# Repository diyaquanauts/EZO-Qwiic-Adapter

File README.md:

# EZO Qwiic Adapter
This is a simple qwiic I2C adapter for Atlas Scientifics isolated carrier board.
## Assembled Board

## Bare Board

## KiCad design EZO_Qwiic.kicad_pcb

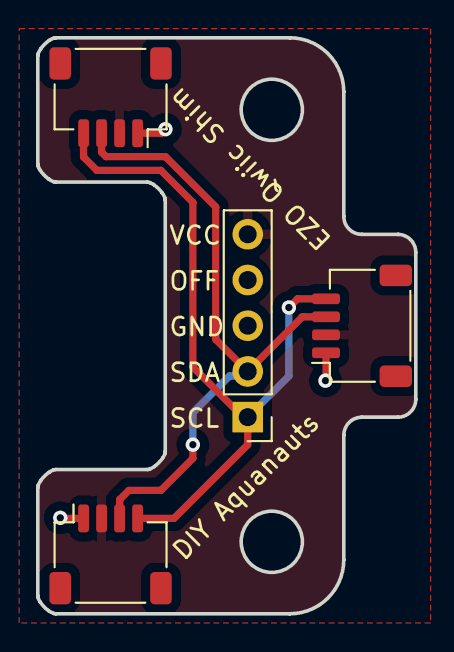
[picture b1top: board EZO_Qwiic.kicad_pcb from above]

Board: 2 copper layers, 21.0 x 32.0 mm, 4 parts (0 on the bottom side), 4 nets.

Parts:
J1: Conn_01x05_Male; PinHeader_1x05_P2.54mm_Vertical
J2, J3, J4: Conn_01x04_Male; JST_SH_SM04B-SRSS-TB_1x04-1MP_P1.00mm_Horizontal

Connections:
/SCL: J1.1, J2.4, J3.4, J4.4
/SDA: J1.2, J2.3, J3.3, J4.3
GND: J1.3, J2.1, J3.1, J4.1
VCC: J1.5, J2.2, J3.2, J4.2

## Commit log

2023-10-23 Add readme
